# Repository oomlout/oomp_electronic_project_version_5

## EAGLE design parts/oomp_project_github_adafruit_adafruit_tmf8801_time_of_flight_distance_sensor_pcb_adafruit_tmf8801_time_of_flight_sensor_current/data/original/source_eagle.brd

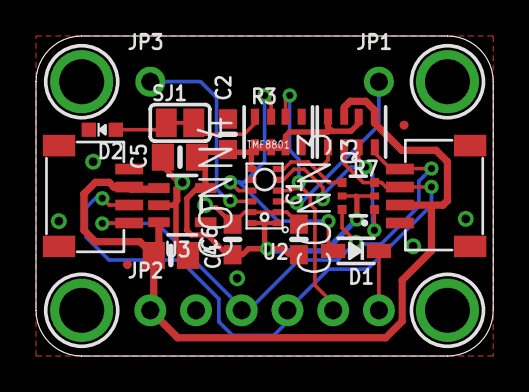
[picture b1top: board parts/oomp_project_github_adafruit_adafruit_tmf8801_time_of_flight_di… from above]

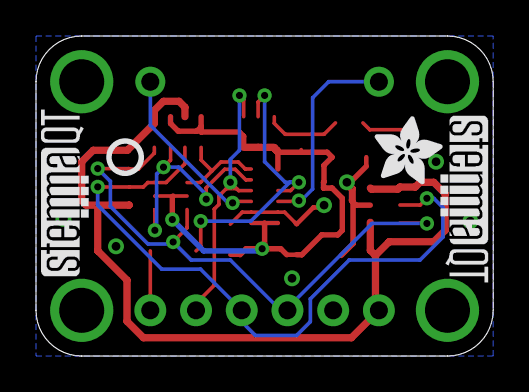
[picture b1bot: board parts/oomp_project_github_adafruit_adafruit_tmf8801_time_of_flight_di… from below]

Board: 2 copper layers, 25.4 x 17.8 mm, 43 parts (8 on the bottom side), 14 nets.

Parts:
C1, C2, C6: 0.1uF; 0603-NO
C4, C5: 10uF; 0805-NO
CONN3, CONN4: STEMMA_I2C_QT; JST_SH4
D1: 1N4148; SOD-323
D2: GREEN; CHIPLED_0603_NOOUTLINE
FID1, FID4: FIDUCIAL_0.5MM
JP1, JP3: 1X01_ROUND
JP2: 1X06_ROUND_70
PLABEL0: PLABEL0
PLABEL1: PLABEL1
PLABEL2: PLABEL2
PLABEL3: PLABEL3
PLABEL4: PLABEL4
PLABEL5: PLABEL5
PLABEL7: PLABEL7
PLABEL8: PLABEL8
PLABEL9: PLABEL9
PLABEL10: PLABEL10
PLABEL12: PLABEL12
PLABEL14: PLABEL14
PLABEL15: PLABEL15
PLABEL16: PLABEL16
PLABEL17: PLABEL17
Q3: BSS138; SOT363
R3, R7: 10K Pack; RESPACK_4X0603
SJ1: SOLDERJUMPER_CLOSEDWIRE
U2: TMF8801; TMF880X
U3: AP2112K-3.3; SOT23-5
U$30, U$31, U$33, U$34: MOUNTINGHOLE2.5; MOUNTINGHOLE_2.5_PLATED
U$36: ADAFRUIT_3.5MM
U$37: PCBFEAT-REV-040
U$38, U$39: STEMMAQT

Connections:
3.3V: C1.1, C2.1, C5.1, C6.1, Q3.2, Q3.5, R3.1, R3.2, R3.3, R7.2, R7.4, U2.1, U2.7, U2.12, U3.5
EN: D1.C, JP2.6
EN_3V: D1.A, R3.7, U2.9
GND: C1.2, C2.2, C4.2, C5.2, C6.2, CONN3.1, CONN3.MT1, CONN3.MT2, CONN4.1, CONN4.MT1, CONN4.MT2, D2.C, JP2.2, U2.2, U2.8, U2.11, U3.2
GPIO0: JP1.1, U2.3
GPIO1: JP3.1, U2.10
INT: JP2.5, R3.6, U2.4
unnamed: R3.8, SJ1.2
unnamed: D2.A, SJ1.1
SCL: CONN3.4, CONN4.4, JP2.3, Q3.6, R7.8
SCL_3V: Q3.1, R7.7, U2.5
SDA: CONN3.3, CONN4.3, JP2.4, Q3.3, R7.6
SDA_3V: Q3.4, R7.5, U2.6
VCC: C4.1, CONN3.2, CONN4.2, JP2.1, R7.1, R7.3, U3.1, U3.3

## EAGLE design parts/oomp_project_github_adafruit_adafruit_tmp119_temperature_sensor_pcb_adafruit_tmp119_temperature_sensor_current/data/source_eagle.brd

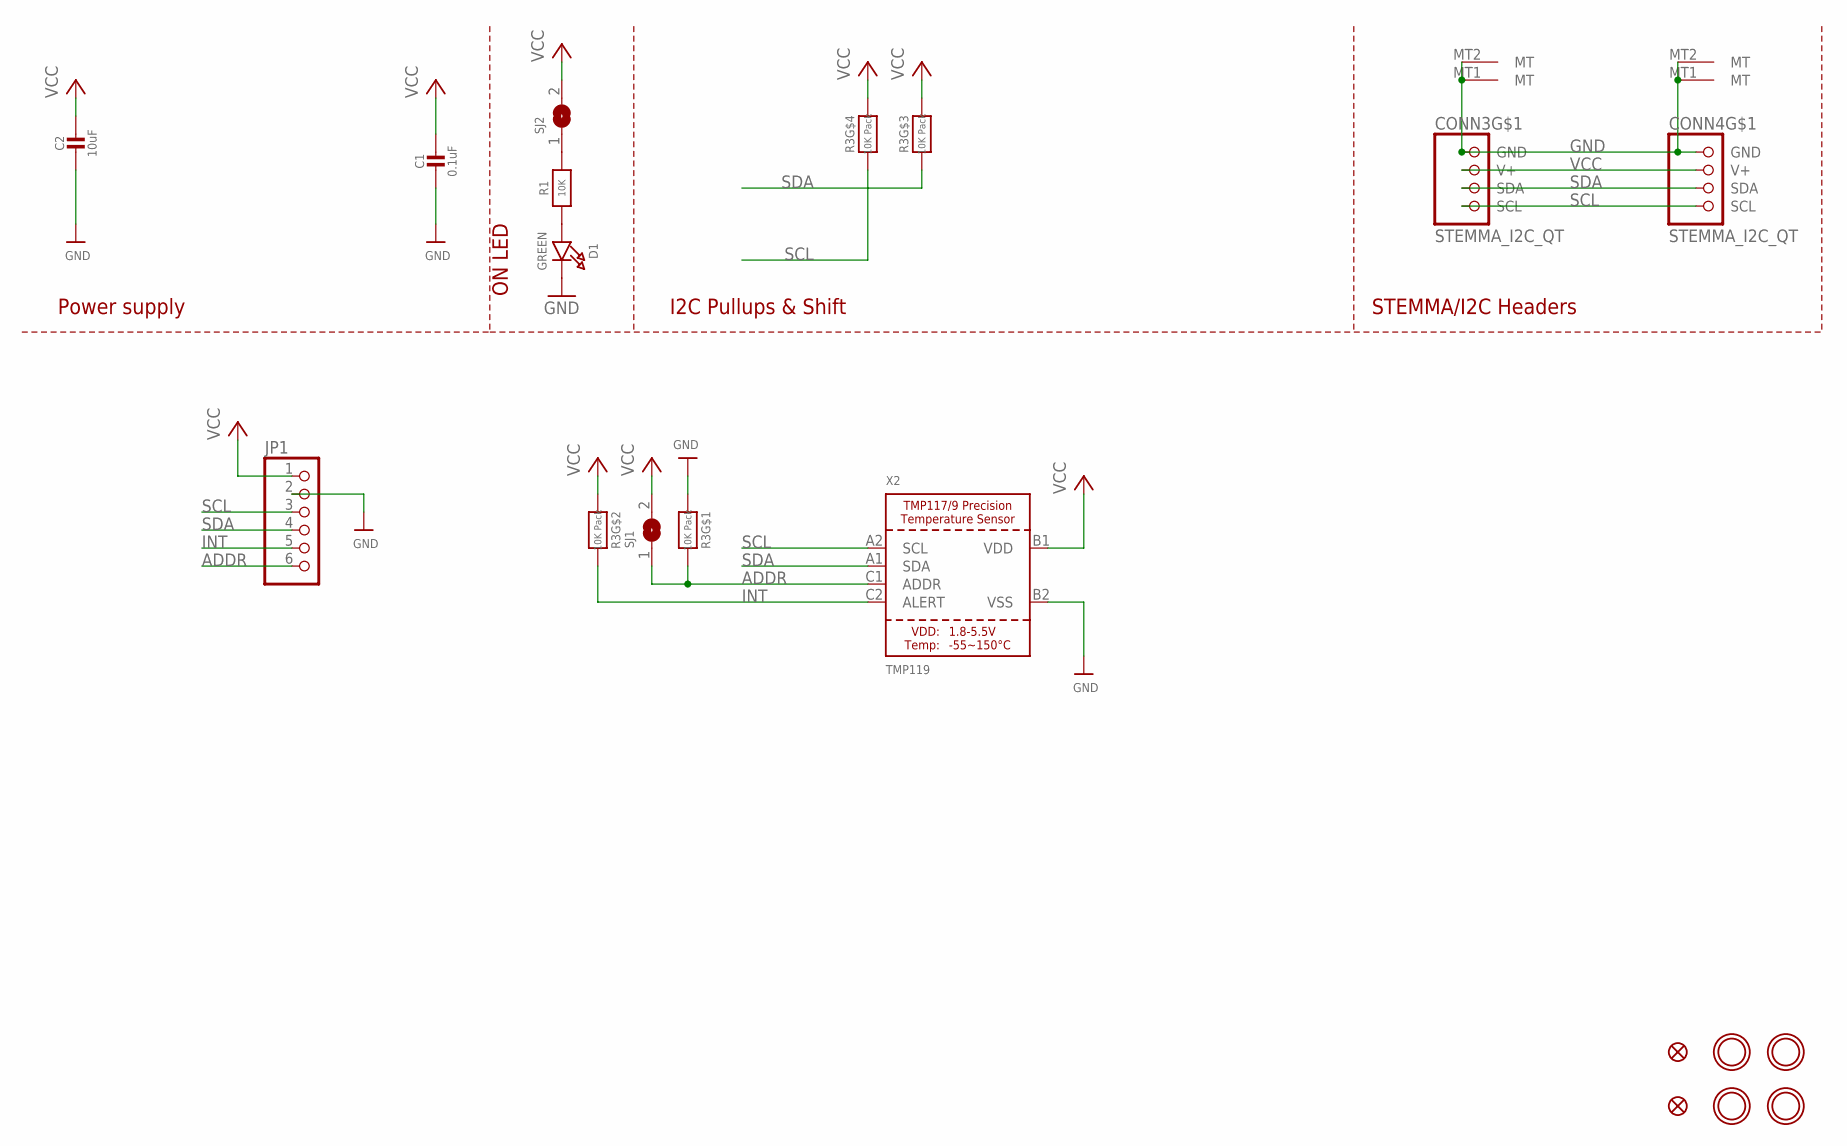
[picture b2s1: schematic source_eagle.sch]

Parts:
C1: 0.1uF; 0603-NO
C2: 10uF; 0805-NO
CONN3, CONN4: STEMMA_I2C_QT; JST_SH4
D1: GREEN; CHIPLED_0603_NOOUTLINE
FID3, FID4: FIDUCIAL_0.5MM
JP1: HEADER-1X670MIL; 1X06_ROUND_70
R1: 10K; 0603-NO
R3: 10K Pack; RESPACK_4X0603
SJ1: SOLDERJUMPER; SOLDERJUMPER_ARROW_NOPASTE
SJ2: SOLDERJUMPERCLOSED; SOLDERJUMPER_CLOSEDWIRE
U$1, U$17, U$19, U$21: MOUNTINGHOLE2.5; MOUNTINGHOLE_2.5_PLATED
X2: TMP119; DSBGA-9

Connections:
ADDR: JP1.6, R3.8 (2), SJ1.1, X2.C1 (ADDR)
GND: C1.2, C2.2, CONN3.1 (GND), CONN3.MT1 (MT), CONN3.MT2 (MT), CONN4.1 (GND), CONN4.MT1 (MT), CONN4.MT2 (MT), D1.C, JP1.2, R3.1, X2.B2 (VSS)
INT: JP1.5, R3.7 (2), X2.C2 (ALERT)
unnamed: D1.A, R1.1
unnamed: R1.2, SJ2.1
SCL: CONN3.4 (SCL), CONN4.4 (SCL), JP1.3, R3.4 (1), X2.A2 (SCL)
SDA: CONN3.3 (SDA), CONN4.3 (SDA), JP1.4, R3.3 (1), X2.A1 (SDA)
VCC: C1.1, C2.1, CONN3.2 (V+), CONN4.2 (V+), JP1.1, R3.2 (1), R3.5 (2), R3.6 (2), SJ1.2, SJ2.2, X2.B1 (VDD)

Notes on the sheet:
I2C Pullups & Shift
STEMMA/I2C Headers
ON LED
Power supply

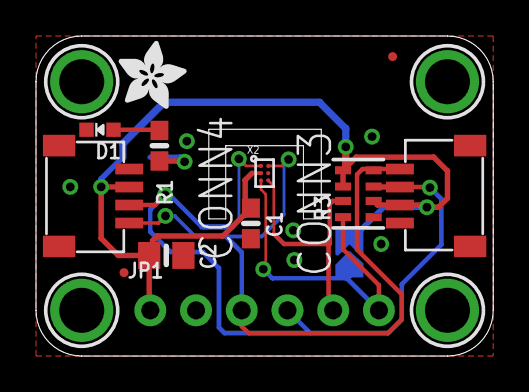
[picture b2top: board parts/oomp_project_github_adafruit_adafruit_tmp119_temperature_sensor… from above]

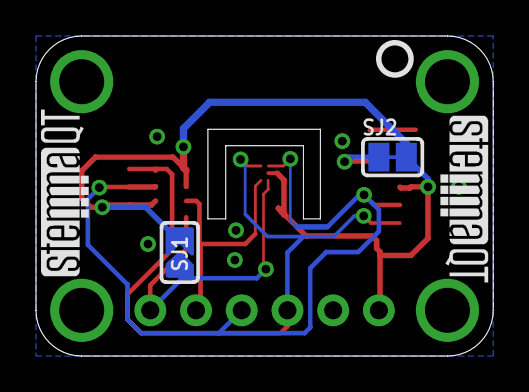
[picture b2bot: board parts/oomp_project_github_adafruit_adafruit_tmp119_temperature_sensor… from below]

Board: 2 copper layers, 25.4 x 17.8 mm, 37 parts (12 on the bottom side), 8 nets.

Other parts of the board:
PLABEL0: PLABEL0
PLABEL1: PLABEL1
PLABEL2: PLABEL2
PLABEL3: PLABEL3
PLABEL4: PLABEL4
PLABEL5: PLABEL5
PLABEL6: PLABEL6
PLABEL7: PLABEL7
PLABEL8: PLABEL8
PLABEL9: PLABEL9
PLABEL10: PLABEL10
PLABEL11: PLABEL11
PLABEL12: PLABEL12
PLABEL13: PLABEL13
PLABEL14: PLABEL14
PLABEL15: PLABEL15
U$22: ADAFRUIT_3.5MM
U$25: PCBFEAT-REV-040
U$30, U$31: STEMMAQT

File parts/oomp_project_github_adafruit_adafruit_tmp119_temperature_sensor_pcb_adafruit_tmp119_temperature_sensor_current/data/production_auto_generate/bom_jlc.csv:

Comment,Designator,Footprint,LCSC Part #
,JP1,Adafruit TMP119 Temperature Sensor-import-fps:1X06_ROUND_70,C37208
,U$22,Adafruit TMP119 Temperature Sensor-import-fps:ADAFRUIT_3.5MM,
,U$25,Adafruit TMP119 Temperature Sensor-import-fps:PCBFEAT-REV-040,
,PLABEL0,Adafruit TMP119 Temperature Sensor-import-fps:PLABEL0,
,PLABEL1,Adafruit TMP119 Temperature Sensor-import-fps:PLABEL1,
,PLABEL10,Adafruit TMP119 Temperature Sensor-import-fps:PLABEL10,
,PLABEL11,Adafruit TMP119 Temperature Sensor-import-fps:PLABEL11,
,PLABEL12,Adafruit TMP119 Temperature Sensor-import-fps:PLABEL12,
,PLABEL13,Adafruit TMP119 Temperature Sensor-import-fps:PLABEL13,
,PLABEL14,Adafruit TMP119 Temperature Sensor-import-fps:PLABEL14,
,PLABEL15,Adafruit TMP119 Temperature Sensor-import-fps:PLABEL15,
,PLABEL2,Adafruit TMP119 Temperature Sensor-import-fps:PLABEL2,
,PLABEL3,Adafruit TMP119 Temperature Sensor-import-fps:PLABEL3,
,PLABEL4,Adafruit TMP119 Temperature Sensor-import-fps:PLABEL4,
,PLABEL5,Adafruit TMP119 Temperature Sensor-import-fps:PLABEL5,
,PLABEL6,Adafruit TMP119 Temperature Sensor-import-fps:PLABEL6,
,PLABEL7,Adafruit TMP119 Temperature Sensor-import-fps:PLABEL7,
,PLABEL8,Adafruit TMP119 Temperature Sensor-import-fps:PLABEL8,
,PLABEL9,Adafruit TMP119 Temperature Sensor-import-fps:PLABEL9,
,"U$30,U$31",Adafruit TMP119 Temperature Sensor-import-fps:STEMMAQT,
0.1uF,C1,Adafruit TMP119 Temperature Sensor-import-fps:0603-NO,C14663
10K,R1,Adafruit TMP119 Temperature Sensor-import-fps:0603-NO,C98220
10K Pack,R3,Adafruit TMP119 Temperature Sensor-import-fps:RESPACK_4X0603,C98220
10uF,C2,Adafruit TMP119 Temperature Sensor-import-fps:0805-NO,
GREEN,D1,Adafruit TMP119 Temperature Sensor-import-fps:CHIPLED_0603_NOOUTLINE,
STEMMA_I2C_QT,"CONN3,CONN4",Adafruit TMP119 Temperature Sensor-import-fps:JST_SH4,C160404
TMP119,X2,Adafruit TMP119 Temperature Sensor-import-fps:DSBGA-9,

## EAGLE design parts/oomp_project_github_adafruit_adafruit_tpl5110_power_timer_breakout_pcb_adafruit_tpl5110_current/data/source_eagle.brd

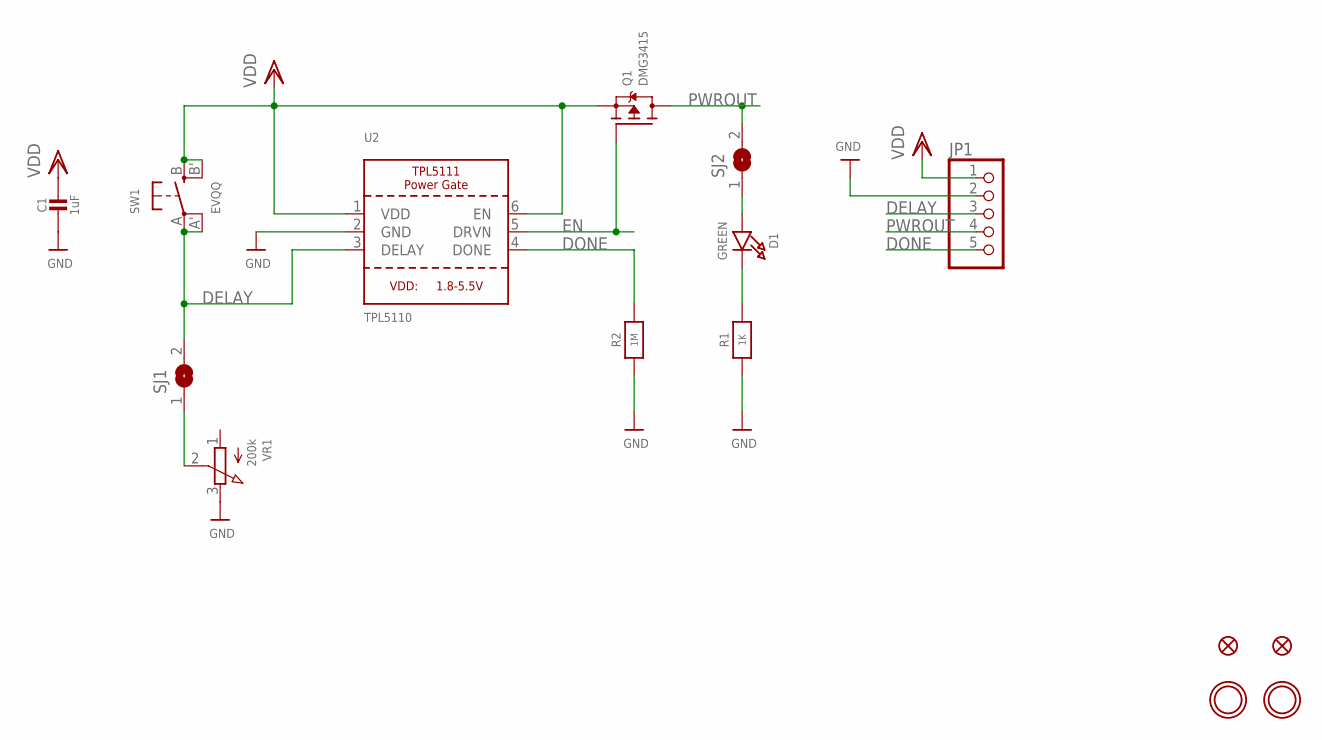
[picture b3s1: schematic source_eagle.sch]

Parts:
C1: 1uF; 0805-NO
D1: GREEN; CHIPLED_0805_NOOUTLINE
FID1, FID2: FIDUCIAL""; FIDUCIAL_1MM
JP1: HEADER-1X570MIL; 1X05_ROUND_70
Q1: DMG3415; SOT23-WIDE
R1: 1K; 0805-NO
R2: 1M; 0805-NO
SJ1, SJ2: SOLDERJUMPERCLOSED; SOLDERJUMPER_CLOSEDWIRE
SW1: EVQQ; EVQ-Q2_SMALLER
U2: TPL5110; SOT23-6
U$7, U$8: MOUNTINGHOLE2.5; MOUNTINGHOLE_2.5_PLATED
VR1: 200k; TRIMPOT_BOURNS_TC33X-2

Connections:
DELAY: JP1.3, SJ1.2, SW1.A, SW1.A' (P1), U2.3 (DELAY)
DONE: JP1.5, R2.2, U2.4 (DONE)
EN: Q1.1 (G), U2.5 (DRVN)
GND: C1.2, JP1.2, R1.1, R2.1, U2.2 (GND), VR1.3 (E)
unnamed: SJ1.1, VR1.2 (S)
unnamed: D1.A, SJ2.1
unnamed: D1.C, R1.2
PWROUT: JP1.4, Q1.3 (D), SJ2.2
VDD: C1.1, JP1.1, Q1.2 (S), SW1.B (S), SW1.B' (S1), U2.1 (VDD), U2.6 (EN)

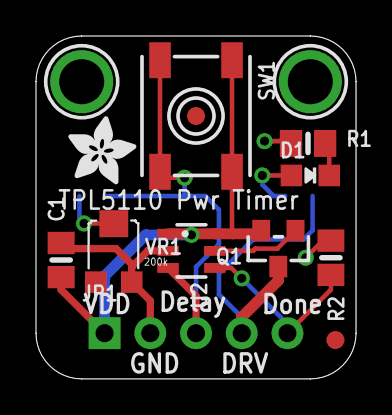
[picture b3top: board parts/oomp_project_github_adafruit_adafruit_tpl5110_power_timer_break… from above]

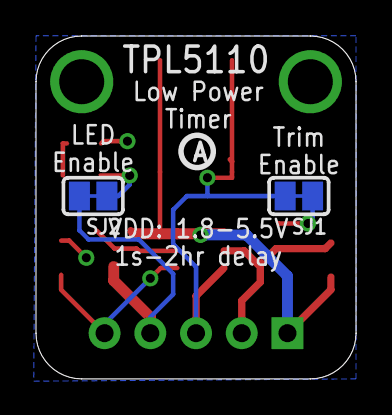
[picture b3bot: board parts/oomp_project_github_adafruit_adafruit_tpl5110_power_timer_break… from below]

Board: 2 copper layers, 17.8 x 19.1 mm, 17 parts (3 on the bottom side), 9 nets.

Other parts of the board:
U$5: ADAFRUIT_3.5MM
U$11: PCBFEAT-REV-040

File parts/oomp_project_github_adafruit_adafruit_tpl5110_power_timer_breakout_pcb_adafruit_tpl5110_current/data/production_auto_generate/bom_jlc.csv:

Comment,Designator,Footprint,LCSC Part #
,JP1,Adafruit TPL5110-import-fps:1X05_ROUND_70,C42431835
,U$5,Adafruit TPL5110-import-fps:ADAFRUIT_3.5MM,
,U$11,Adafruit TPL5110-import-fps:PCBFEAT-REV-040,
1K,R1,Adafruit TPL5110-import-fps:0805-NO,C17513
1M,R2,Adafruit TPL5110-import-fps:0805-NO,C2933280
1uF,C1,Adafruit TPL5110-import-fps:0805-NO,
200k,VR1,Adafruit TPL5110-import-fps:TRIMPOT_BOURNS_TC33X-2,
DMG3415,Q1,Adafruit TPL5110-import-fps:SOT23-WIDE,
EVQQ,SW1,Adafruit TPL5110-import-fps:EVQ-Q2_SMALLER,
GREEN,D1,Adafruit TPL5110-import-fps:CHIPLED_0805_NOOUTLINE,
TPL5110,U2,Adafruit TPL5110-import-fps:SOT23-6,

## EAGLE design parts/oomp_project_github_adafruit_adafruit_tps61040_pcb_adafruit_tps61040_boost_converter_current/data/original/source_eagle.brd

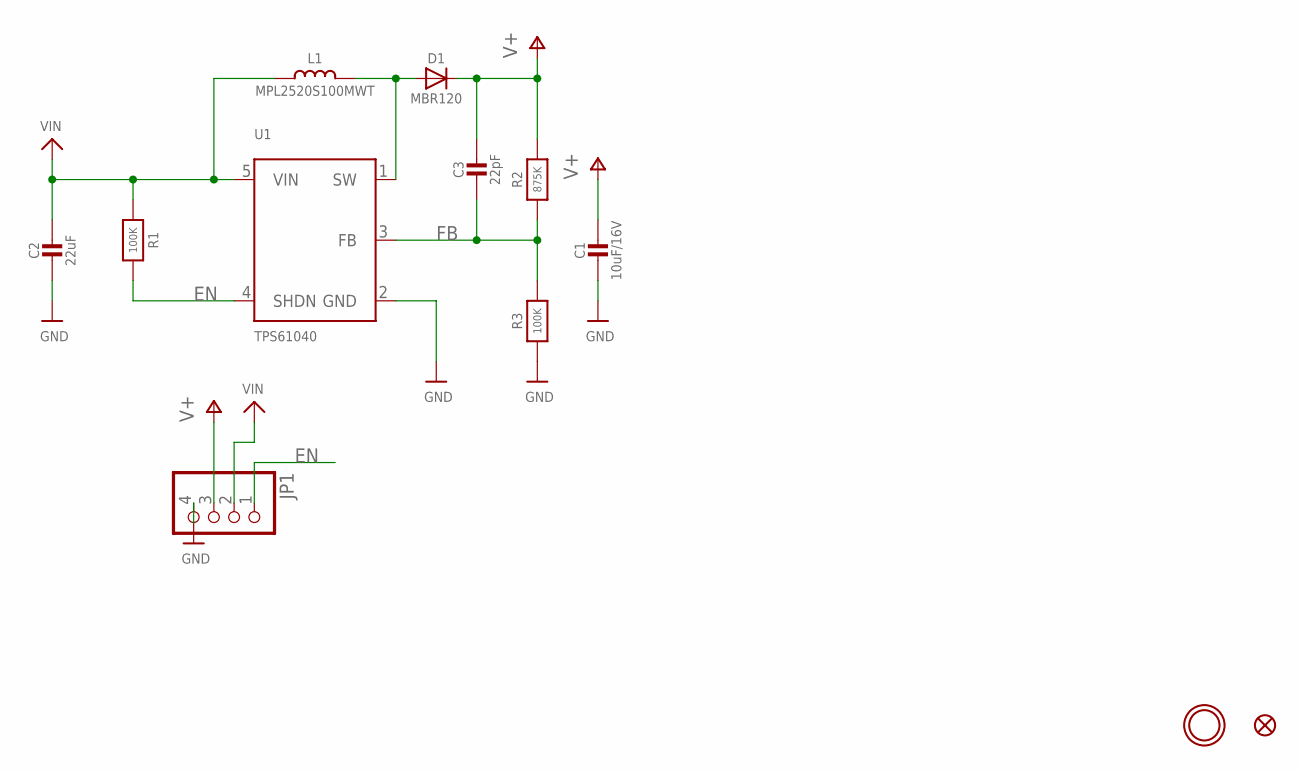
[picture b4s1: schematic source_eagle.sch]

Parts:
C1: 10uF/16V; 0805-NO
C2: 22uF; 0805-NO
C3: 22pF; 0603-NO
D1: MBR120; SOD-123FL
FID1: FIDUCIAL_1MM
JP1: HEADER-1X4ROUND; 1X04_ROUND
L1: MPL2520S100MWT; INDUCTOR_1007
R1, R3: 100K; 0603-NO
R2: 875K; 0603-NO
U1: TPS61040; SOT23-5
U$9: MOUNTINGHOLE2.5; MOUNTINGHOLE_2.5_PLATED

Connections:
EN: JP1.1, R1.2, U1.4 (SHDN)
FB: C3.2, R2.1, R3.2, U1.3 (FB)
GND: C1.2, C2.2, JP1.4, R3.1, U1.2 (GND)
unnamed: D1.A, L1.P$2 (2), U1.1 (SW)
V+: C1.1, C3.1, D1.C, JP1.3, R2.2
VIN: C2.1, JP1.2, L1.P$1 (1), R1.1, U1.5 (VIN)

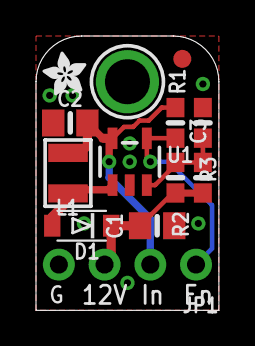
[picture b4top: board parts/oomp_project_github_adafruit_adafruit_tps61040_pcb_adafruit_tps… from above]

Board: 2 copper layers, 10.2 x 15.2 mm, 14 parts (1 on the bottom side), 6 nets.

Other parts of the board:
U$10: PCBFEAT-REV-040
U$11: ADAFRUIT_2.5MM

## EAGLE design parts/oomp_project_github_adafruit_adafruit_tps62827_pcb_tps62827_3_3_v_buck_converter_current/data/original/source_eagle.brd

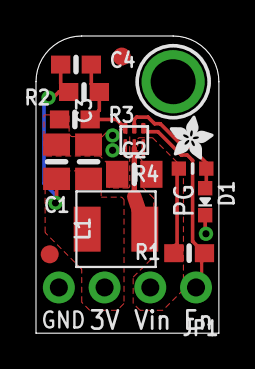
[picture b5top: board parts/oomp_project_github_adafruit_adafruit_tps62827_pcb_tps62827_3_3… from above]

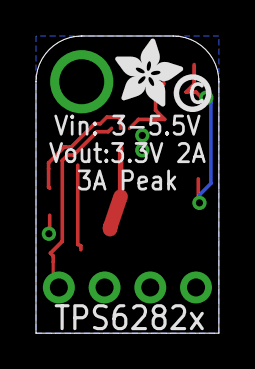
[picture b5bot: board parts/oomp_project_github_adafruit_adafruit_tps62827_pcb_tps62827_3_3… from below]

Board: 2 copper layers, 10.2 x 16.5 mm, 18 parts (2 on the bottom side), 7 nets.

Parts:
C1, C2, C3: 22uF; 0805-NO
C4: 120pF; 0603-NO
D1: green; CHIPLED_0603_NOOUTLINE
FID1, FID2: FIDUCIAL_1MM
IC2: TPS6282X; VSON_6
JP1: 1X04_ROUND
L1: SDER041H-2R2MS; INDUCTOR_4X4MM_SRP0415
R1, R3: 100K; 0603-NO
R2: 450K; 0603-NO
R4: 10k; _0603MP
U$9: MOUNTINGHOLE2.5; MOUNTINGHOLE_2.5_PLATED
U$10: PCBFEAT-REV-040
U$11: ADAFRUIT_2.5MM
U$18: ADAFRUIT_3.5MM

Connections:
3.3V: C1.1, C3.1, C4.1, JP1.3, L1.P$2, R2.2
EN: IC2.P$1, JP1.1, R1.2
FB: C4.2, IC2.P$3, R2.1, R3.2
GND: C1.2, C2.2, C3.2, D1.C, IC2.P$4, JP1.4, R3.1
unnamed: IC2.P$5, L1.P$1
unnamed: D1.A, IC2.P$2, R4.1
VIN: C2.1, IC2.P$6, JP1.2, R1.1, R4.2

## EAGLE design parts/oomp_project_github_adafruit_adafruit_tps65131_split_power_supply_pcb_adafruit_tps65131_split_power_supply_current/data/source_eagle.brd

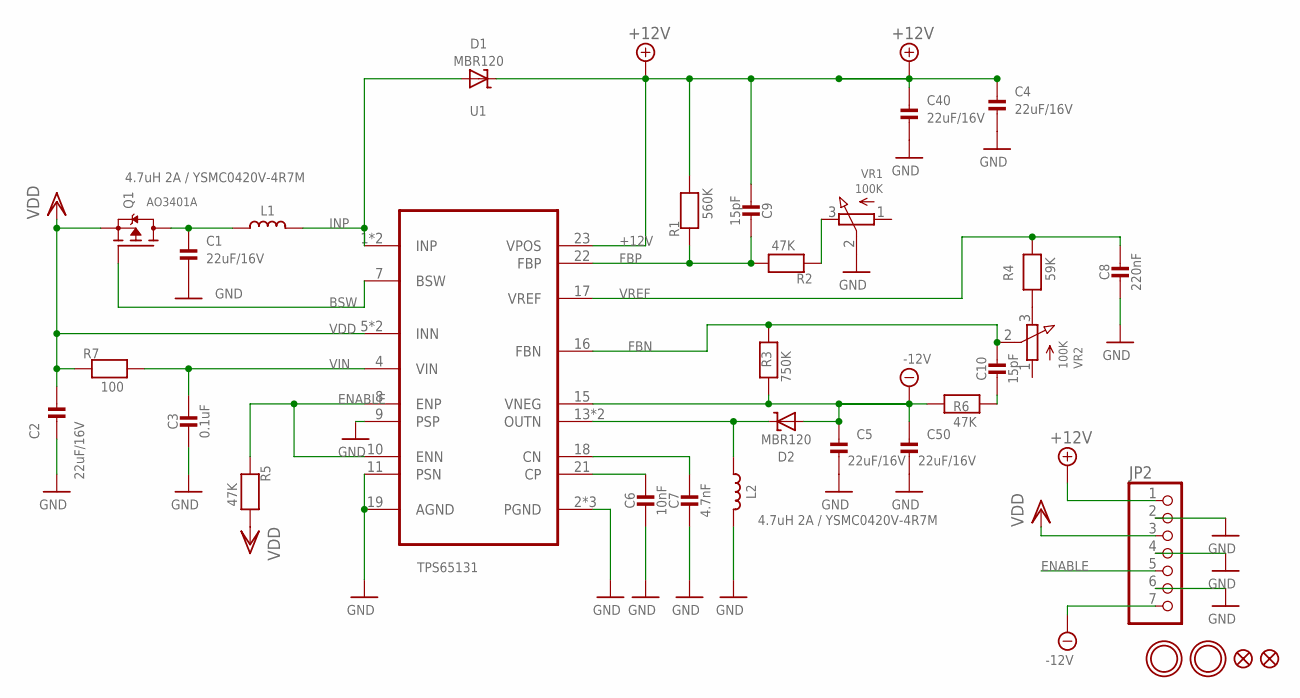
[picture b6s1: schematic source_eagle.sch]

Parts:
C1, C2, C4, C5, C40, C50: 22uF/16V; 0805-NO
C3: 0.1uF; 0603-NO
C6: 10nF; 0603-NO
C7: 4.7nF; 0603-NO
C8: 220nF; 0603-NO
C9, C10: 15pF; 0603-NO
D1, D2: MBR120; SOD-123FL
FID1, FID2: FIDUCIAL_0.5MM
JP2: HEADER-1X7THICKER; 1X07_ROUND_76
L1, L2: 4.7uH 2A / YSMC0420V-4R7M; INDUCTOR_4X4MM_NR401
Q1: AO3401A; SOT23-WIDE
R1: 560K; 0603-NO
R2, R5, R6: 47K; 0603-NO
R3: 750K; 0603-NO
R4: 59K; 0603-NO
R7: 100; 0603-NO
U1: TPS65131; QFN24_4MM
U$1, U$2: MOUNTINGHOLE2.5; MOUNTINGHOLE_2.5_PLATED
VR1, VR2: 100K; TRIMPOT_BOURNS_TC33X-2

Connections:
+12V: C4.2, C9.1, C40.2, D1.C, JP2.1, R1.2, U1.23 (VPOS)
-12V: C5.2, C50.2, D2.A, JP2.7, R3.1, R6.1, U1.15 (VNEG)
BSW: Q1.1 (G), U1.7 (BSW)
ENABLE: JP2.5, R5.1, U1.8 (ENP), U1.10 (ENN)
FBN: C10.2, R3.2, U1.16 (FBN), VR2.2 (S)
FBP: C9.2, R1.1, R2.2, U1.22 (FBP)
GND: C1.1, C2.1, C3.1, C4.1, C5.1, C6.1, C7.1, C8.1, C40.1, C50.1, JP2.2, JP2.4, JP2.6, L2.P$2 (2), U1.2 (PGND), U1.3 (PGND), U1.9 (PSP), U1.11 (PSN), U1.19 (AGND), U1.25 (PGND), VR1.2 (S)
INP: D1.A, L1.P$2 (2), U1.1 (INP), U1.24 (INP)
unnamed: C6.2, U1.21 (CP)
unnamed: C1.2, L1.P$1 (1), Q1.3 (D)
unnamed: R2.1, VR1.3 (E)
unnamed: R4.1, VR2.3 (E)
unnamed: C10.1, R6.2
unnamed: C7.2, U1.18 (CN)
OUTN: D2.C, L2.P$1 (1), U1.13 (OUTN), U1.14 (OUTN)
VDD: C2.2, JP2.3, Q1.2 (S), R5.2, R7.1, U1.5 (INN), U1.6 (INN)
VIN: C3.2, R7.2, U1.4 (VIN)
VREF: C8.2, R4.2, U1.17 (VREF)

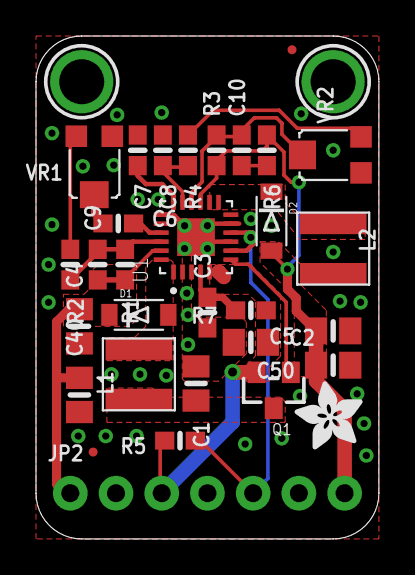
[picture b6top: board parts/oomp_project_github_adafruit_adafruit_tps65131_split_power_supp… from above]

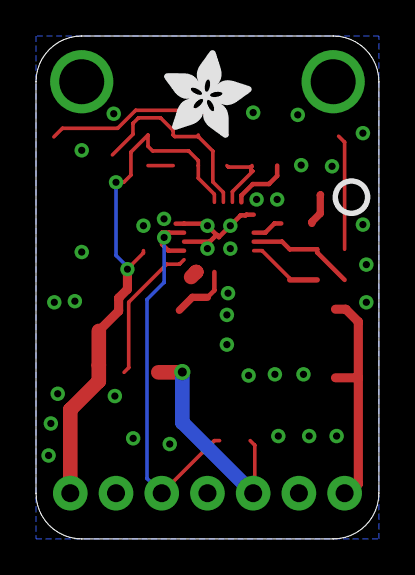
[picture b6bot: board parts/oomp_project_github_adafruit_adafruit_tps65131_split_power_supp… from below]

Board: 2 copper layers, 19.1 x 27.9 mm, 47 parts (4 on the bottom side), 18 nets.

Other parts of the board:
PLABEL0: PLABEL0
PLABEL1: PLABEL1
PLABEL2: PLABEL2
PLABEL3: PLABEL3
PLABEL4: PLABEL4
PLABEL5: PLABEL5
PLABEL6: PLABEL6
PLABEL7: PLABEL7
PLABEL8: PLABEL8
PLABEL9: PLABEL9
PLABEL10: PLABEL10
PLABEL11: PLABEL11
U$3: ADAFRUIT_3.5MM
U$4: ADAFRUIT_5MM
U$5: PCBFEAT-REV-040

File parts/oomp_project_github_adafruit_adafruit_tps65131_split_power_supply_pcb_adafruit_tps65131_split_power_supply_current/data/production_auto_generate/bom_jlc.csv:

Comment,Designator,Footprint,LCSC Part #
,JP2,Adafruit TPS65131 Split Power Supply-import-fps:1X07_ROUND_76,C7501585
,U$3,Adafruit TPS65131 Split Power Supply-import-fps:ADAFRUIT_3.5MM,
,U$4,Adafruit TPS65131 Split Power Supply-import-fps:ADAFRUIT_5MM,
,U$5,Adafruit TPS65131 Split Power Supply-import-fps:PCBFEAT-REV-040,
,PLABEL0,Adafruit TPS65131 Split Power Supply-import-fps:PLABEL0,
,PLABEL1,Adafruit TPS65131 Split Power Supply-import-fps:PLABEL1,
,PLABEL10,Adafruit TPS65131 Split Power Supply-import-fps:PLABEL10,
,PLABEL11,Adafruit TPS65131 Split Power Supply-import-fps:PLABEL11,
,PLABEL2,Adafruit TPS65131 Split Power Supply-import-fps:PLABEL2,
,PLABEL3,Adafruit TPS65131 Split Power Supply-import-fps:PLABEL3,
,PLABEL4,Adafruit TPS65131 Split Power Supply-import-fps:PLABEL4,
,PLABEL5,Adafruit TPS65131 Split Power Supply-import-fps:PLABEL5,
,PLABEL6,Adafruit TPS65131 Split Power Supply-import-fps:PLABEL6,
,PLABEL7,Adafruit TPS65131 Split Power Supply-import-fps:PLABEL7,
,PLABEL8,Adafruit TPS65131 Split Power Supply-import-fps:PLABEL8,
,PLABEL9,Adafruit TPS65131 Split Power Supply-import-fps:PLABEL9,
0.1uF,C3,Adafruit TPS65131 Split Power Supply-import-fps:0603-NO,C14663
100,R7,Adafruit TPS65131 Split Power Supply-import-fps:0603-NO,C22775
100K,"VR1,VR2",Adafruit TPS65131 Split Power Supply-import-fps:TRIMPOT_BOURNS_TC33X-2,
10nF,C6,Adafruit TPS65131 Split Power Supply-import-fps:0603-NO,C5137477
15pF,"C9,C10",Adafruit TPS65131 Split Power Supply-import-fps:0603-NO,
220nF,C8,Adafruit TPS65131 Split Power Supply-import-fps:0603-NO,
22uF/16V,"C1,C2,C4,C5,C40,C50",Adafruit TPS65131 Split Power Supply-import-fps:0805-NO,
4.7nF,C7,Adafruit TPS65131 Split Power Supply-import-fps:0603-NO,
4.7uH 2A / YSMC0420V-4R7M,"L1,L2",Adafruit TPS65131 Split Power Supply-import-fps:INDUCTOR_4X4MM_NR401,
47K,"R2,R5,R6",Adafruit TPS65131 Split Power Supply-import-fps:0603-NO,C2907042
560K,R1,Adafruit TPS65131 Split Power Supply-import-fps:0603-NO,C2907051
59K,R4,Adafruit TPS65131 Split Power Supply-import-fps:0603-NO,
750K,R3,Adafruit TPS65131 Split Power Supply-import-fps:0603-NO,C23240
AO3401A,Q1,Adafruit TPS65131 Split Power Supply-import-fps:SOT23-WIDE,
MBR120,"D1,D2",Adafruit TPS65131 Split Power Supply-import-fps:SOD-123FL,
TPS65131,U1,Adafruit TPS65131 Split Power Supply-import-fps:QFN24_4MM,

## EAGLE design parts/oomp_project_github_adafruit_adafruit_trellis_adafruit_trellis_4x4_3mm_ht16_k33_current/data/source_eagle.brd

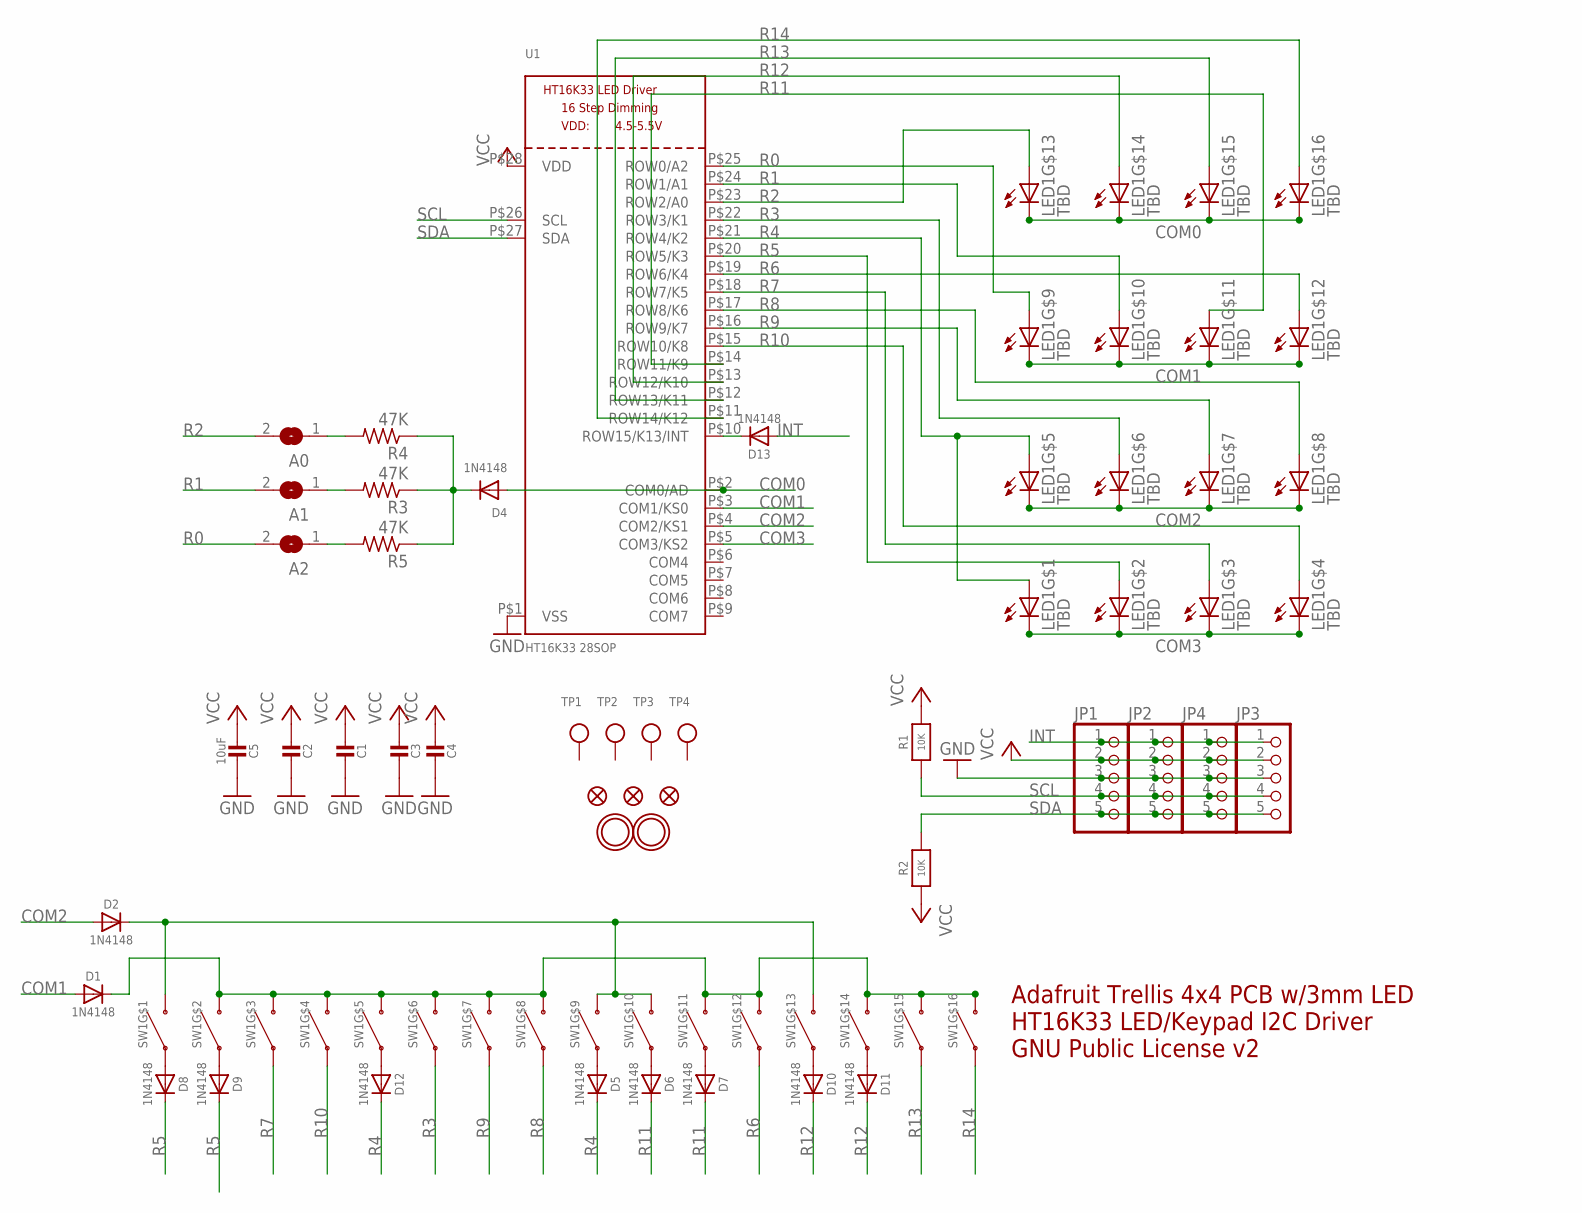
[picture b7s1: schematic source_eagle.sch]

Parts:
A0, A1, A2: SOLDERJUMPERREFLOW_NOPASTE; SOLDERJUMPER_REFLOW_NOPASTE
C1, C2, C3, C4: CAP_CERAMIC_0805; _0805
C5: 10uF; _0805
D1, D2, D5, D6, D7, D8, D9, D10, D11, D12, D13: 1N4148; SOD-323
D4: 1N4148; SOD-323F
FID1, FID2, FID3: FIDUCIAL""; FIDUCIAL_1MM
JP1, JP2, JP3, JP4: HEADER-1X5EDGESMT; 1X5_SMT
LED1: TBD; LED3MM-4X4GRID
R1, R2: 10K; _0805
R3, R4, R5: 47K; R0805
SW1: SWITCH-SILICON-4X4GRID-10MM-5.4MM; ELAST_PAD_SQUARE_10MM_5.4MM_4X4GRID
TP1, TP2, TP3, TP4: TESTPOINT; TESTPOINT_SMT
U1: HT16K33 28SOP; SOP28_300MIL
U$1, U$2: MOUNTINGHOLE2.5; MOUNTINGHOLE_2.5_PLATED

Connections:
COM0: D4.A, LED1.K13 (C), LED1.K14 (C), LED1.K15 (C), LED1.K16 (C), U1.P$2 (COM0/AD)
COM1: D1.A, LED1.K9 (C), LED1.K10 (C), LED1.K11 (C), LED1.K12 (C), U1.P$3 (COM1/KS0)
COM2: D2.A, LED1.K5 (C), LED1.K6 (C), LED1.K7 (C), LED1.K8 (C), U1.P$4 (COM2/KS1)
COM3: LED1.K1 (C), LED1.K2 (C), LED1.K3 (C), LED1.K4 (C), U1.P$5 (COM3/KS2)
GND: C1.1, C2.1, C3.1, C4.1, C5.1, JP1.3, JP2.3, JP3.3, JP4.3, U1.P$1 (VSS)
INT: D13.A, JP1.1, JP2.1, JP3.1, JP4.1
unnamed: D2.C, SW1.B1, SW1.B9, SW1.B10, SW1.B13
unnamed: D13.C, U1.P$10 (ROW15/K13/INT)
unnamed: D5.A, SW1.A9
unnamed: D6.A, SW1.A10
unnamed: D1.C, SW1.B2, SW1.B3, SW1.B4, SW1.B5, SW1.B6, SW1.B7, SW1.B8, SW1.B11, SW1.B12, SW1.B14, SW1.B15, SW1.B16
unnamed: D7.A, SW1.A11
unnamed: D8.A, SW1.A1
unnamed: D9.A, SW1.A2
unnamed: A2.1, R5.2
unnamed: D10.A, SW1.A13
unnamed: D11.A, SW1.A14
unnamed: D12.A, SW1.A5
unnamed: D4.C, R3.1, R4.1, R5.1
unnamed: A1.1, R3.2
unnamed: A0.1, R4.2
R0: A2.2, LED1.A9 (A), U1.P$25 (ROW0/A2)
R1: A1.2, LED1.A10 (A), U1.P$24 (ROW1/A1)
R2: A0.2, LED1.A13 (A), U1.P$23 (ROW2/A0)
R3: LED1.A6 (A), SW1.A6, U1.P$22 (ROW3/K1)
R4: D5.C, D12.C, LED1.A1 (A), LED1.A5 (A), U1.P$21 (ROW4/K2)
R5: D8.C, D9.C, LED1.A2 (A), U1.P$20 (ROW5/K3)
R6: LED1.A12 (A), SW1.A12, U1.P$19 (ROW6/K4)
R7: LED1.A3 (A), SW1.A3, U1.P$18 (ROW7/K5)
R8: LED1.A8 (A), SW1.A8, U1.P$17 (ROW8/K6)
R9: LED1.A7 (A), SW1.A7, U1.P$16 (ROW9/K7)
R10: LED1.A4 (A), SW1.A4, U1.P$15 (ROW10/K8)
R11: D6.C, D7.C, LED1.A11 (A), U1.P$14 (ROW11/K9)
R12: D10.C, D11.C, LED1.A14 (A), U1.P$13 (ROW12/K10)
R13: LED1.A15 (A), SW1.A15, U1.P$12 (ROW13/K11)
R14: LED1.A16 (A), SW1.A16, U1.P$11 (ROW14/K12)
SCL: JP1.4, JP2.4, JP3.4, JP4.4, R1.1, U1.P$26 (SCL)
SDA: JP1.5, JP2.5, JP3.5, JP4.5, R2.2, U1.P$27 (SDA)
VCC: C1.2, C2.2, C3.2, C4.2, C5.2, JP1.2, JP2.2, JP3.2, JP4.2, R1.2, R2.1, U1.P$28 (VDD)

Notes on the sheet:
Adafruit Trellis 4x4 PCB w/3mm LED HT16K33 LED/Keypad I2C Driver GNU Public License v2

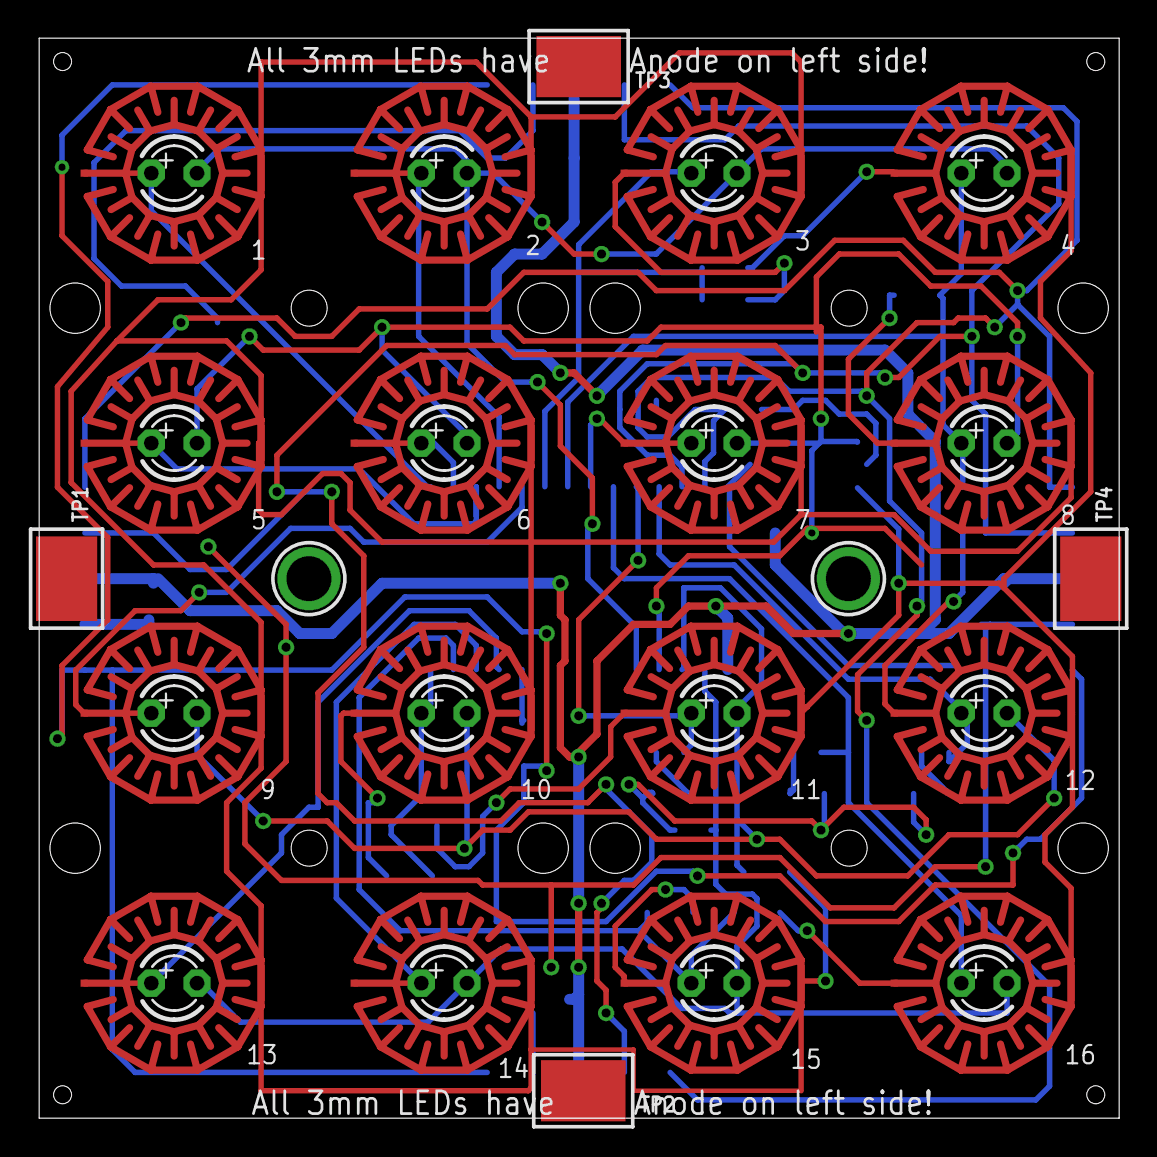
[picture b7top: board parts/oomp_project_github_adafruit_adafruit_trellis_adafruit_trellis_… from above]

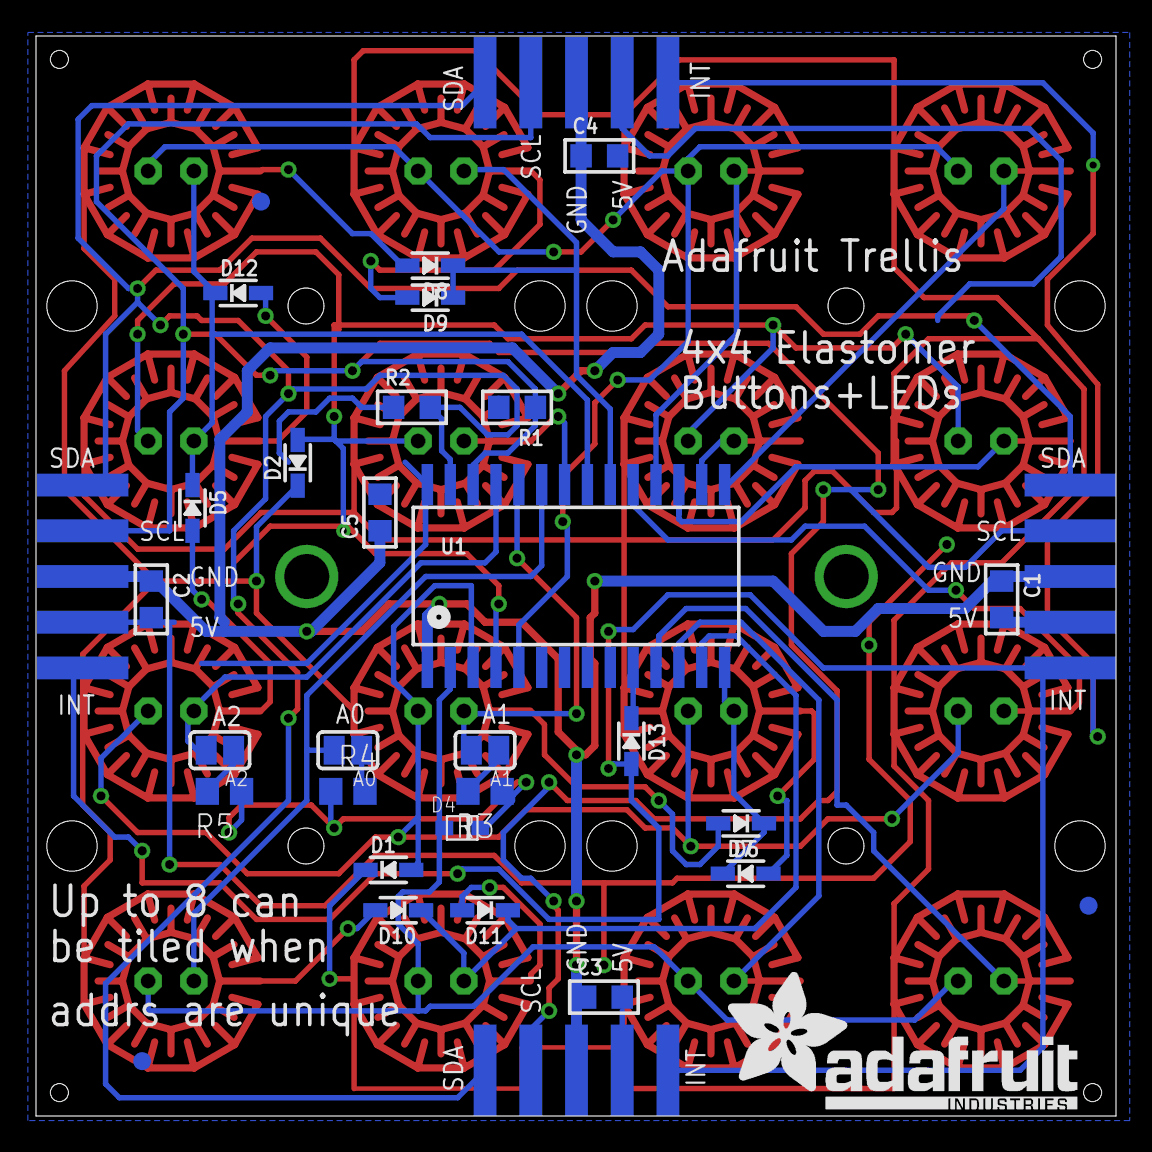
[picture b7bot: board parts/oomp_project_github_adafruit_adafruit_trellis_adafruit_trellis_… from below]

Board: 2 copper layers, 60.0 x 60.0 mm, 42 parts (34 on the bottom side), 39 nets.

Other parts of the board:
U$3: ADAFRUIT_TEXT_20MM

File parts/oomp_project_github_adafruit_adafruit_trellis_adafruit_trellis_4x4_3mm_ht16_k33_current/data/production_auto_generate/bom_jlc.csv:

Comment,Designator,Footprint,LCSC Part #
,"JP1,JP2,JP3,JP4",Adafruit Trellis 4x4 3mm HT16K33-import-fps:1X5_SMT,C42431835
,"C1,C2,C3,C4",Adafruit Trellis 4x4 3mm HT16K33-import-fps:_0805,
,U$3,Adafruit Trellis 4x4 3mm HT16K33-import-fps:ADAFRUIT_TEXT_20MM,
,SW1,Adafruit Trellis 4x4 3mm HT16K33-import-fps:ELAST_PAD_SQUARE_10MM_5.4MM_4X4GRID,
,"A0,A1,A2",Adafruit Trellis 4x4 3mm HT16K33-import-fps:SOLDERJUMPER_REFLOW_NOPASTE,
,"TP1,TP2,TP3,TP4",Adafruit Trellis 4x4 3mm HT16K33-import-fps:TESTPOINT_SMT,
10K,"R1,R2",Adafruit Trellis 4x4 3mm HT16K33-import-fps:_0805,C17414
10uF,C5,Adafruit Trellis 4x4 3mm HT16K33-import-fps:_0805,
1N4148,"D1,D2,D5,D6,D7,D8,D9,D10,D11,D12,D13",Adafruit Trellis 4x4 3mm HT16K33-import-fps:SOD-323,
1N4148,D4,Adafruit Trellis 4x4 3mm HT16K33-import-fps:SOD-323F,
47K,"R3,R4,R5",Adafruit Trellis 4x4 3mm HT16K33-import-fps:R0805,C17713
HT16K33 28SOP,U1,Adafruit Trellis 4x4 3mm HT16K33-import-fps:SOP28_300MIL,
TBD,LED1,Adafruit Trellis 4x4 3mm HT16K33-import-fps:LED3MM-4X4GRID,

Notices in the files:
parts and their libraries:
microbuilder: This work is placed in the public domain, and may be freely used for commercial and non-commercial work with the following conditions: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
